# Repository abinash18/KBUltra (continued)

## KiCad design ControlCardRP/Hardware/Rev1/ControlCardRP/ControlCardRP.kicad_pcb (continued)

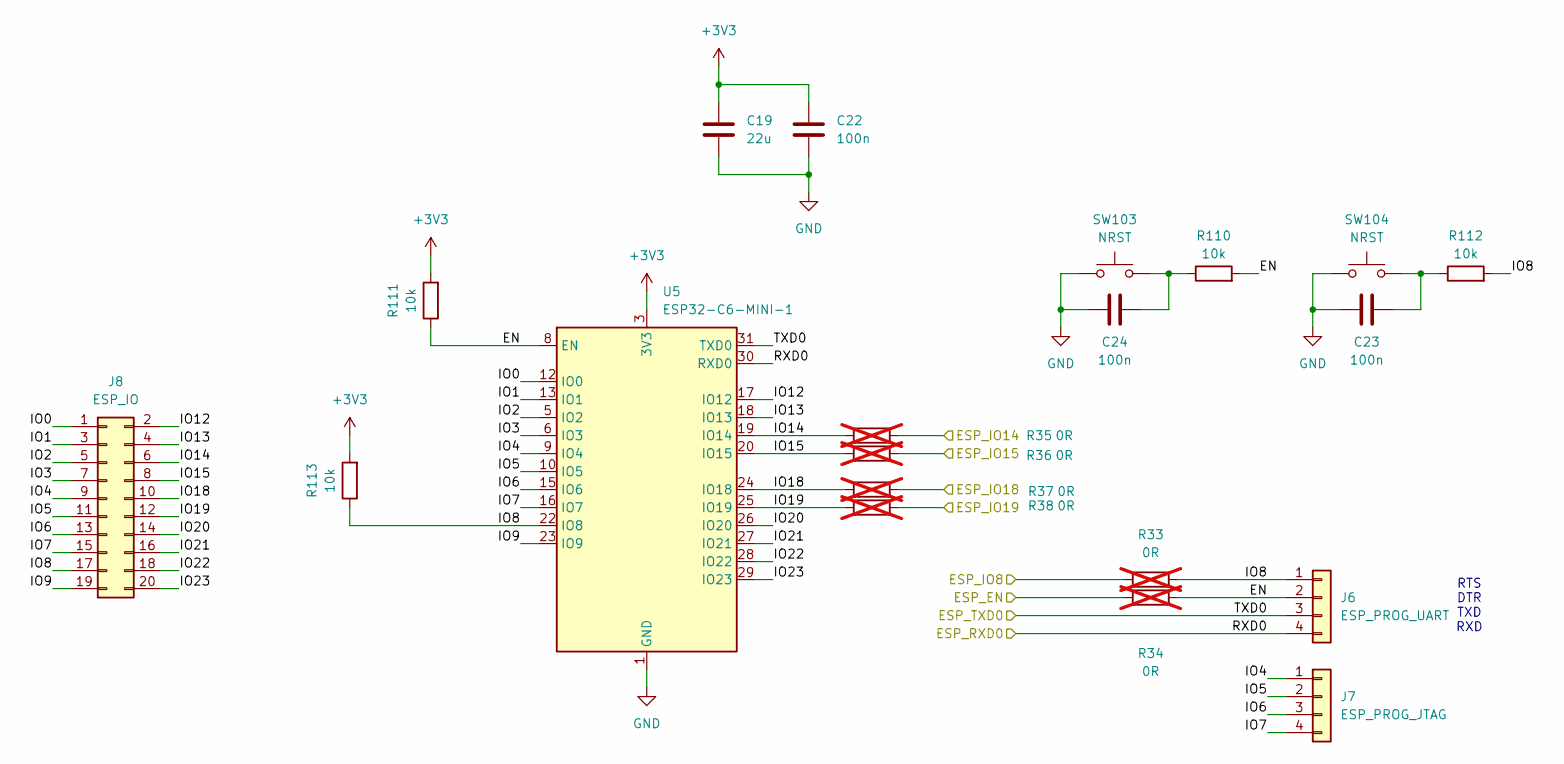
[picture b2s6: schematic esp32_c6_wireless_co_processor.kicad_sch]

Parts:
C19: 22u; C_0603_1608Metric; LCSC Part # C59461
C22, C23, C24: 100n; C_0402_1005Metric; LCSC Part # C1525
J6: ESP_PROG_UART; PinHeader_1x04_P1.27mm_Vertical
J7: ESP_PROG_JTAG; PinHeader_1x04_P1.27mm_Vertical
J8: ESP_IO; PinSocket_2x10_P1.27mm_Vertical_SMD
R33, R34, R35, R36, R37, R38: 0R; R_0402_1005Metric; LCSC Part # C17168; not fitted
R110, R111, R112, R113: 10k; R_0402_1005Metric; LCSC Part # C25744
SW103, SW104: NRST; SW_SPST_PTS810
U5: ESP32-C6-MINI-1

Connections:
+3V3: C19.1, C22.1, R111.2, R113.2, U5.3 (3V3); also elsewhere on the board
/ESP32-C6 Wireless Co-Processor/EN: J6.2, R34.2, R110.2, R111.1, U5.8 (EN)
/ESP32-C6 Wireless Co-Processor/IO0: J8.1, U5.12 (IO0)
/ESP32-C6 Wireless Co-Processor/IO1: J8.3, U5.13 (IO1)
/ESP32-C6 Wireless Co-Processor/IO2: J8.5, U5.5 (IO2)
/ESP32-C6 Wireless Co-Processor/IO3: J8.7, U5.6 (IO3)
/ESP32-C6 Wireless Co-Processor/IO4: J7.1, J8.9, U5.9 (IO4)
/ESP32-C6 Wireless Co-Processor/IO5: J7.2, J8.11, U5.10 (IO5)
/ESP32-C6 Wireless Co-Processor/IO6: J7.3, J8.13, U5.15 (IO6)
/ESP32-C6 Wireless Co-Processor/IO7: J7.4, J8.15, U5.16 (IO7)
/ESP32-C6 Wireless Co-Processor/IO8: J6.1, J8.17, R33.2, R112.2, R113.1, U5.22 (IO8)
/ESP32-C6 Wireless Co-Processor/IO9: J8.19, U5.23 (IO9)
/ESP32-C6 Wireless Co-Processor/IO12: J8.2, U5.17 (IO12)
/ESP32-C6 Wireless Co-Processor/IO13: J8.4, U5.18 (IO13)
/ESP32-C6 Wireless Co-Processor/IO14: J8.6, R35.1, U5.19 (IO14)
/ESP32-C6 Wireless Co-Processor/IO15: J8.8, R36.1, U5.20 (IO15)
/ESP32-C6 Wireless Co-Processor/IO18: J8.10, R37.1, U5.24 (IO18)
/ESP32-C6 Wireless Co-Processor/IO19: J8.12, R38.1, U5.25 (IO19)
/ESP32-C6 Wireless Co-Processor/IO20: J8.14, U5.26 (IO20)
/ESP32-C6 Wireless Co-Processor/IO21: J8.16, U5.27 (IO21)
/ESP32-C6 Wireless Co-Processor/IO22: J8.18, U5.28 (IO22)
/ESP32-C6 Wireless Co-Processor/IO23: J8.20, U5.29 (IO23)
/GPIO10: R33.1; also elsewhere on the board
/GPIO11: R34.1; also elsewhere on the board
/GPIO12: J6.4, U5.30 (RXD0); also elsewhere on the board
/GPIO13: J6.3, U5.31 (TXD0); also elsewhere on the board
/GPIO19: R35.2; also elsewhere on the board
/GPIO20: R36.2; also elsewhere on the board
/GPIO21: R37.2; also elsewhere on the board
/GPIO22: R38.2; also elsewhere on the board
GND: C19.2, C22.2, C23.2, C24.2, SW103.1, SW104.1, U5.1 (GND), U5.2 (GND), U5.11 (GND), U5.14 (GND), U5.36 (GND), U5.37 (GND), U5.38 (GND), U5.39 (GND), U5.40 (GND), U5.41 (GND), U5.42 (GND), U5.43 (GND), U5.44 (GND), U5.45 (GND), U5.46 (GND), U5.47 (GND), U5.48 (GND), U5.49 (GND), U5.50 (GND), U5.51 (GND), U5.52 (GND), U5.53 (GND); also elsewhere on the board
unnamed: C23.1, R112.1, SW104.2
unnamed: C24.1, R110.1, SW103.2

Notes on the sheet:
RTS DTR TXD RXD

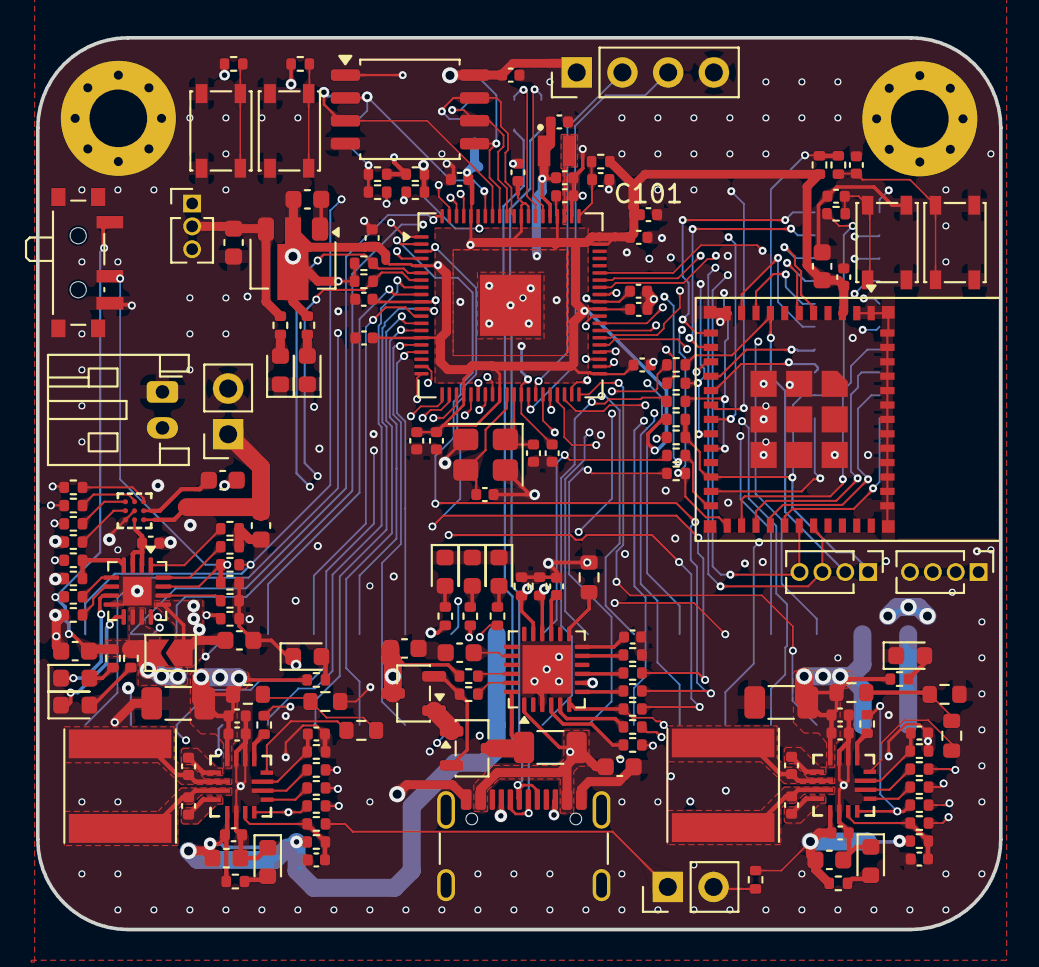
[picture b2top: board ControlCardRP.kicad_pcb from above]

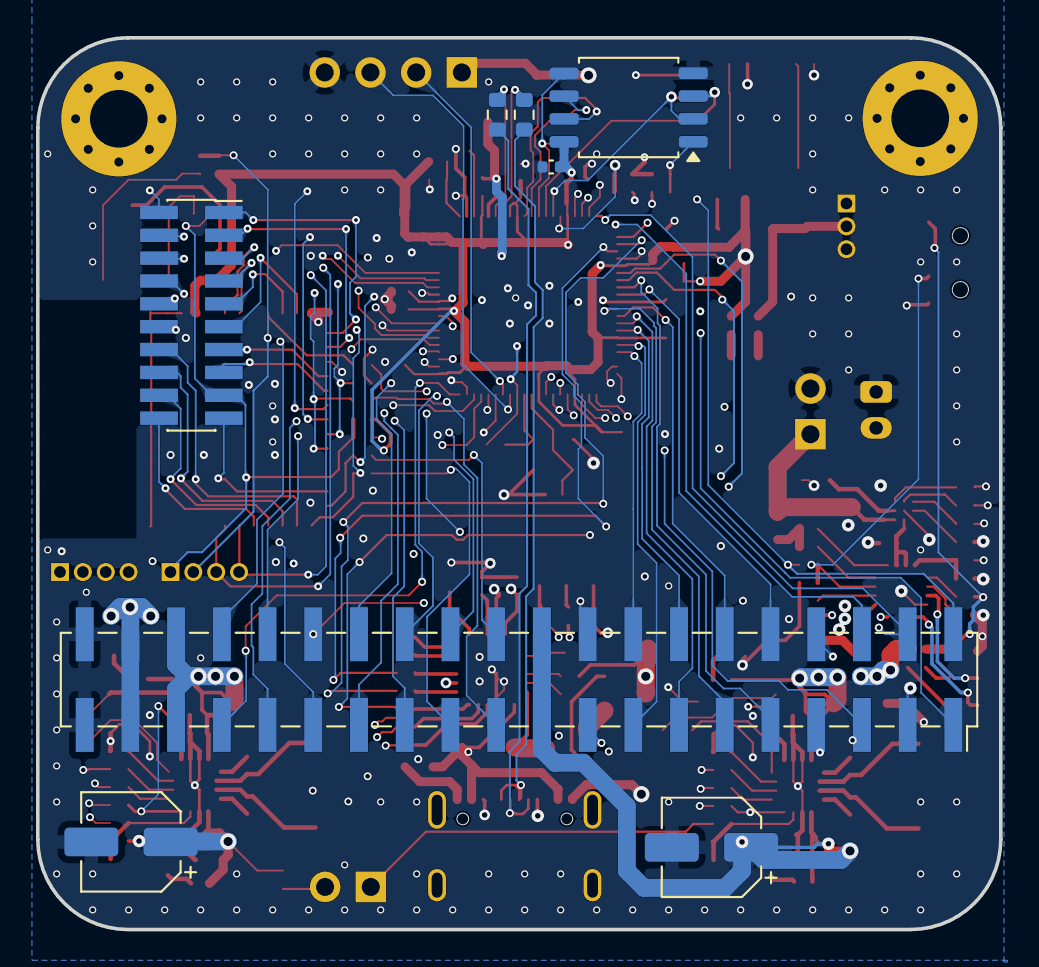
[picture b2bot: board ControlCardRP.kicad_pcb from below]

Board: 4 copper layers, 53.5 x 49.5 mm, 181 parts (8 on the bottom side), 169 nets.

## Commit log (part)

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2026-05-17 Added switches and finished initial layout with leds and stabalizers
2026-05-18 Added RP MCU
